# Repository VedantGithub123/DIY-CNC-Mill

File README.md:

# Project Overview

The goal of this project is to develop a G-code interpreter and CNC mill. The CNC mill can follow straight lines, arcs and cubic bezier curves. It is 3D-printed with PETG, uses stepper motors, which are controlled with an Arduino Mega. The code ran on the laptop sends motor speeds to the Arduino, which moves the motors accordingly. To use the program, connect the Arudino Mega to your laptop with a USB cable. Run the Python file 

## Getting Started

SolidWorks is used for the CAD

KiCAD is used for the circuit diagram and PCB

Ensure Git is installed and setup to work with he repository

Clone the project repository to your local machine and navigate into the directory:
```
git clone https://github.com/VedantGithub123/DIY-CNC-Mill
cd DIY-CNC-Mill
```

Python and the PyGame library are needed

Arduino and the AccelStepper library are needed

## Repository Structure

The `main` branch is the organized working branch. Below is an overview of the folder structure for the `main` branch of this repository
```
DIY-CNC-Mill/
├── build/
├── electrical/
├── input/
├── media/
├── src/
│   ├── arduino/
│   ├── assets/
│   └── run.py
└── README.md
```

### Folder Descriptions

`build/`: Contains files relating to the physical construction of the device

&emsp;&emsp;`design/`: Contains the CAD files of the design

`electrical/`: Contains files relating to the electrical wiring of the device

`input/`: Location of G-code files to run

`media/`: Contains photos of the mill

`src/`: Contains all source code and assets

&emsp;&emsp;`arduino/`: Code to run on the Arduino

&emsp;&emsp;`assets/`: Photos needed for the GUI

&emsp;&emsp;`run.c`: Program to run on the laptop

`README.md`: Project repository documentation

## Program Design Process
Before deciding on how the program specifications were, I needed to determine how I wanted to organize the code. I wanted to keep the UI, G-code interpreter, and serial communication sections separate. A constant loop was needed for the UI, then when buttons are pressed, it would tell the CNC how to move or change the data, such as what file is being read. Finally, during the loop, the interpreter should calculate what speeds are needed and use the serial communication to send it to the Arduino.

### G-Code Protocol
I decided to follow this marlin G-code protocol (mostly): <https://marlinfw.org/meta/gcode/>

However, the only commands that can be used are:
- G0: Straight line max speed
- G1: Straight line controlled
- G2: Clockwise Arc
- G3: Counterclockwise Arc
- G4: Stop for time
- G5: Cubic Bezier Curve
- G9: Stop
- M0/M1/M2/M30: Stop the machine and spindle
- M3: Spindle on clockwise
- M4: Spindle on counterclockwise
- M5: Stop the spindle

### Speed Calculations
The path-following algorithms in `run.py` use the same control approach for straight lines, arcs, and cubic Bezier curves. Each path can provide a position and tangent for a given parameter, allowing the main update loop to follow different G-code commands without duplicating the motion-control logic.

During each update, the program determines the point on the active path that is closest to the current spindle position. It calculates the tangent at that point and combines it with a correction vector from the spindle to the path. The correction keeps the tool close to the programmed path, while the tangent continues the motion toward the end of the command. This produces the velocity vector that `run.py` sends to the Arduino through the serial connection.

The requested velocity is then constrained by the machine's acceleration and deceleration limits. At the beginning of a movement, the speed increases gradually. As the spindle approaches the endpoint, the speed is reduced so the target can be reached without overshooting. If the next movement is compatible with the current direction, the code can transition directly into it instead of stopping between commands; commands such as stops and dwells require the velocity to reach zero.

The update loop repeats these calculations while the machine is running. When the spindle is sufficiently close to the endpoint and its remaining velocity is small enough, `run.py` completes the current command and advances to the next one. This separates path geometry, speed limiting, and serial output while allowing the same motion loop to control lines, arcs, and Bezier curves.

### Serial Communication Protocol
When the computer tries to connect with the Arduino, the Arduino will say `CNC Ready`. The computer will need to read this before continuing. The Python program opens the Arduino's serial connection, waits for this ready message, and then begins sending movement and spindle commands generated by the G-code interpreter.

The Arduino program reads the commands received over the serial connection, converts them into motor and spindle actions, and uses the stepper-motor controllers to execute them. It continues processing incoming commands while the machine is running and reports status messages back to the computer when necessary. The Python program reads these responses so that it can keep the user interface and machine state synchronized.

If the ready message is not received, the Python program should not send movement commands. The Arduino must be connected over USB and powered before starting the Python program.

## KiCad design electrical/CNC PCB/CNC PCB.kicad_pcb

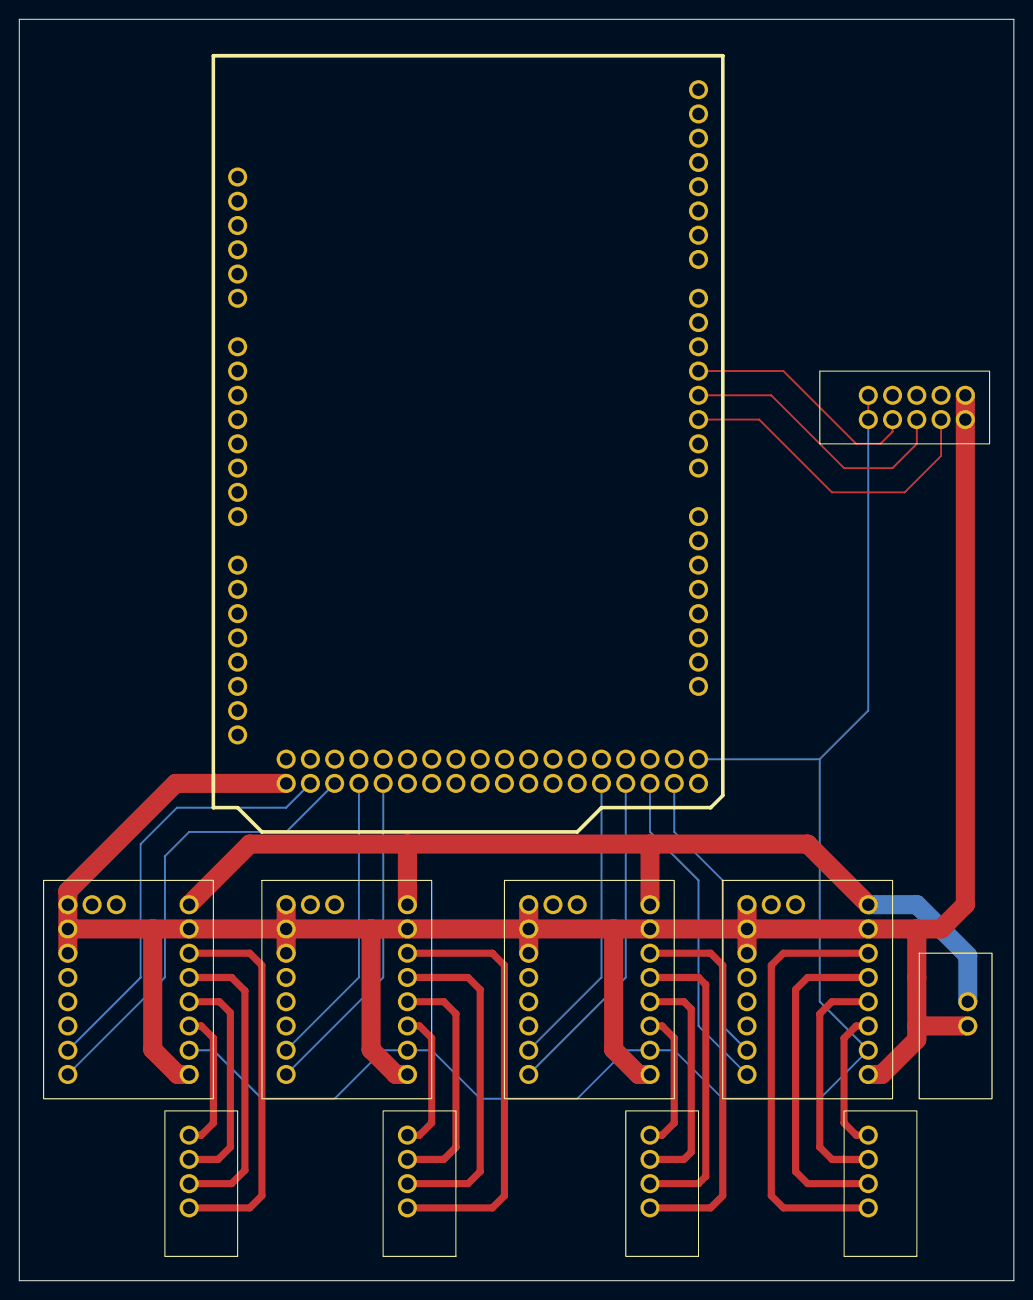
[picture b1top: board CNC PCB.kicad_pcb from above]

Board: 2 copper layers, 104.1 x 132.1 mm, 11 parts (0 on the bottom side), 30 nets.

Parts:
J1: Stepper 1; 4 Pin Connector
J2: Stepper 2; 4 Pin Connector
J3: Stepper 3; 4 Pin Connector
J4: Stepper 4; 4 Pin Connector
J5: 12V Power Source; 2 Pin Connector
SHIELD1: ARDUINO_MEGA_SHIELD; ARDUINO MEGA SHIELD
U1: Stepper Driver 1; TMC2209
U2: Stepper Driver 2; TMC2209
U3: Stepper Driver 3; TMC2209
U4: Stepper Driver 4; TMC2209
U5: Motor Driver; L298

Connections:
+5V: SHIELD1.5V_4, U1.15 (VDD), U2.15 (VDD), U3.15 (VDD), U4.15 (VDD), U5.1 (+5V), U5.6 (+5V)
+12V: J5.1, U1.9 (VM), U2.9 (VM), U3.9 (VM), U4.9 (VM)
/A1_1: J1.2, U1.12 (A1)
/A1_2: J2.2, U2.12 (A1)
/A1_3: J3.2, U3.12 (A1)
/A1_4: J4.2, U4.12 (A1)
/A2_1: J1.1, U1.11 (A2)
/A2_2: J2.1, U2.11 (A2)
/A2_3: J3.1, U3.11 (A2)
/A2_4: J4.1, U4.11 (A2)
/B1_1: J1.3, U1.13 (B1)
/B1_2: J2.3, U2.13 (B1)
/B1_3: J3.3, U3.13 (B1)
/B1_4: J4.3, U4.13 (B1)
/B2_1: J1.4, U1.14 (B2)
/B2_2: J2.4, U2.14 (B2)
/B2_3: J3.4, U3.14 (B2)
/B2_4: J4.4, U4.14 (B2)
/DIR_1: SHIELD1.25 (PA3), U1.8 (DIR)
/DIR_2: SHIELD1.27 (PA5), U2.8 (DIR)
/DIR_3: SHIELD1.47 (PL2), U3.8 (DIR)
/DIR_4: SHIELD1.51 (PB2_(MOSI)), U4.8 (DIR)
/ENA: SHIELD1.4, U5.2 (ENA)
/IN1: SHIELD1.3, U5.3 (IN1)
/IN2: SHIELD1.2, U5.4 (IN2)
/STEP_1: SHIELD1.23 (PA1), U1.7 (STEP)
/STEP_2: SHIELD1.29 (PA7), U2.7 (STEP)
/STEP_3: SHIELD1.49 (PL0), U3.7 (STEP)
/STEP_4: SHIELD1.53 (PB0_(SS)), U4.7 (STEP)
GND: J5.2, SHIELD1.GND5, U1.1 (EN), U1.2 (MS1), U1.3 (MS2), U1.10 (GND), U1.16 (GND), U2.1 (EN), U2.2 (MS1), U2.3 (MS2), U2.10 (GND), U2.16 (GND), U3.1 (EN), U3.2 (MS1), U3.3 (MS2), U3.10 (GND), U3.16 (GND), U4.1 (EN), U4.2 (MS1), U4.3 (MS2), U4.10 (GND), U4.16 (GND), U5.5 (GND), U5.10 (GND)

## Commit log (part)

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2025-08-22 Changed CAD Model
